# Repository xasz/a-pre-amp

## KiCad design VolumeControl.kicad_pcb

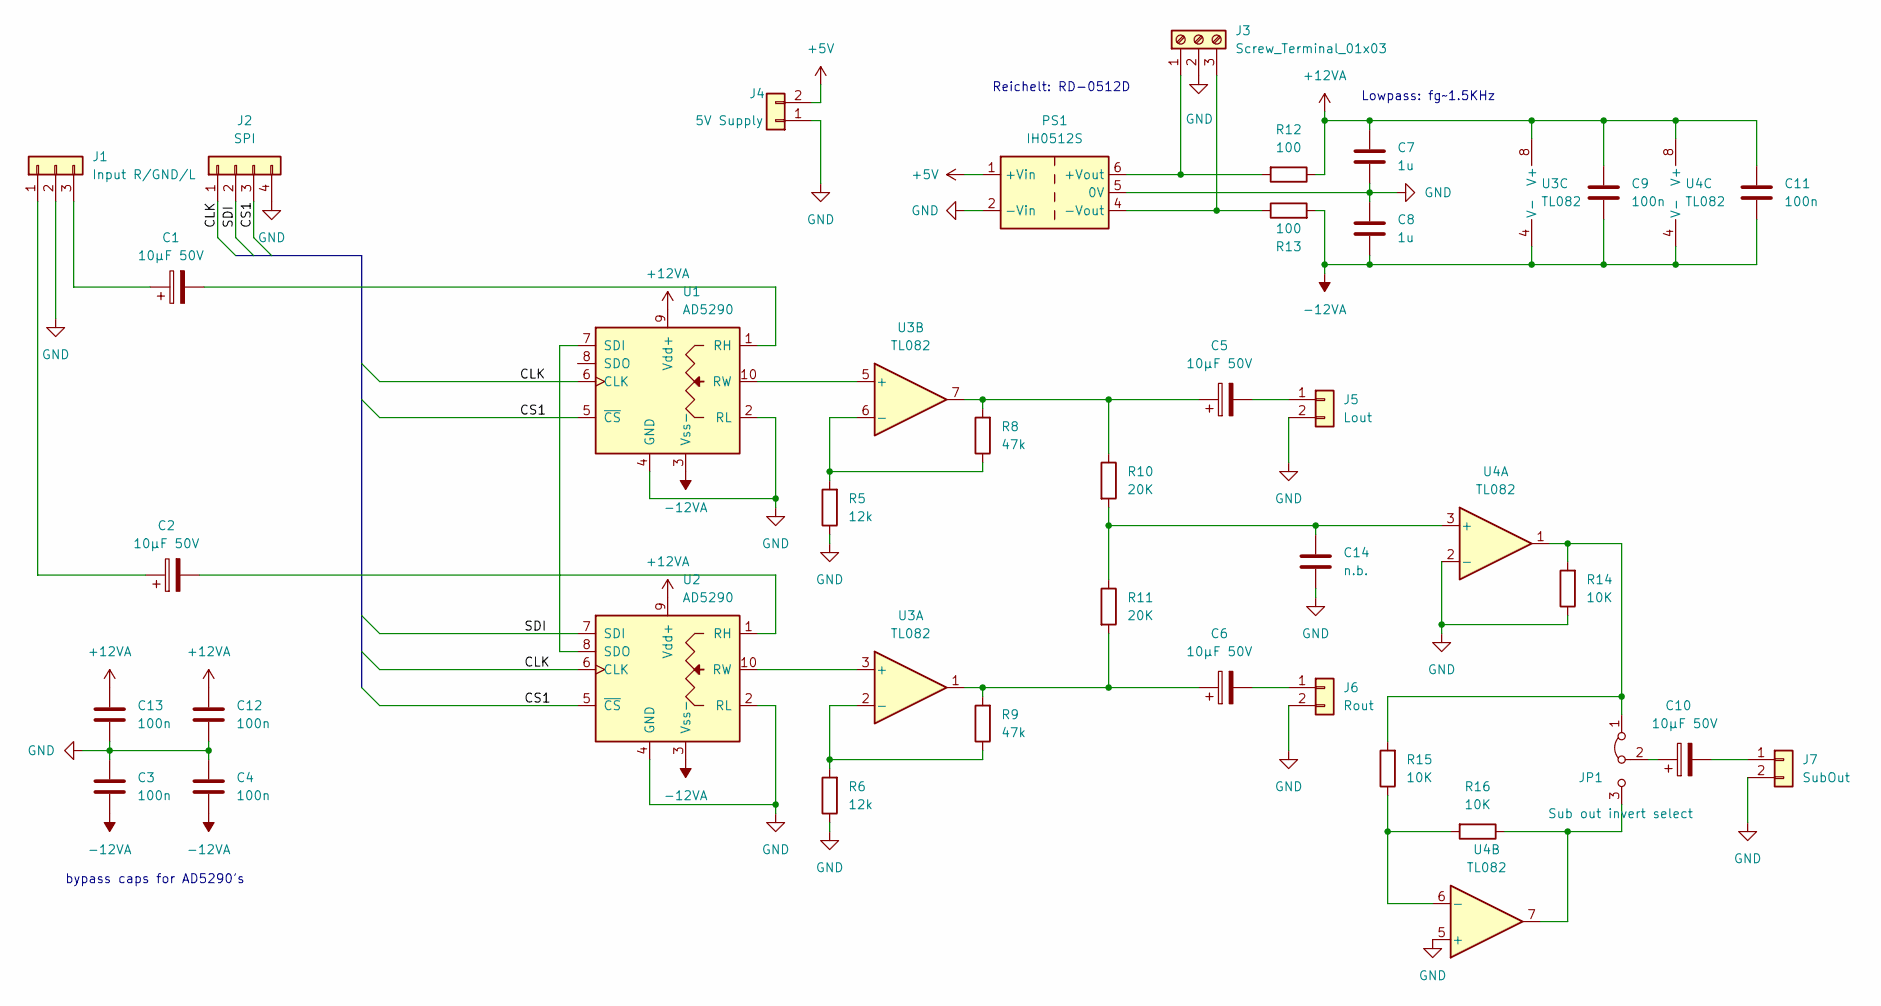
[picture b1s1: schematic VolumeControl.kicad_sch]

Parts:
C1, C2, C5, C6, C10: 10µF 50V; CP_Radial_D5.0mm_P2.00mm
C3, C4, C9, C11, C12, C13: 100n; C_Rect_L4.6mm_W2.0mm_P2.50mm_MKS02_FKP02
C7, C8: 1u; C_Rect_L7.0mm_W2.5mm_P5.00mm
C14: n.b.; C_Rect_L7.0mm_W2.5mm_P5.00mm
J1: Input R/GND/L; JST_XH_B3B-XH-A_1x03_P2.50mm_Vertical
J2: SPI; PinHeader_1x04_P2.54mm_Vertical
J3: Screw_Terminal_01x03; TerminalBlock_Phoenix_PT-1,5-3-5.0-H_1x03_P5.00mm_Horizontal
J4: 5V Supply; PinHeader_1x02_P2.54mm_Vertical
J5: Lout; Molex_KK-254_AE-6410-02A_1x02_P2.54mm_Vertical
J6: Rout; Molex_KK-254_AE-6410-02A_1x02_P2.54mm_Vertical
J7: SubOut; Molex_KK-254_AE-6410-02A_1x02_P2.54mm_Vertical
JP1: Sub out invert select; PinHeader_1x03_P2.54mm_Vertical
PS1: IH0512S; Converter_DCDC_XP_POWER-IHxxxxS_THT
R5, R6: 12k; R_Axial_DIN0207_L6.3mm_D2.5mm_P10.16mm_Horizontal
R8, R9: 47k; R_Axial_DIN0207_L6.3mm_D2.5mm_P10.16mm_Horizontal
R10, R11: 20K; R_Axial_DIN0207_L6.3mm_D2.5mm_P10.16mm_Horizontal
R12, R13: 100; R_Axial_DIN0207_L6.3mm_D2.5mm_P10.16mm_Horizontal
R14, R15, R16: 10K; R_Axial_DIN0207_L6.3mm_D2.5mm_P10.16mm_Horizontal
U1, U2: AD5290; MSOP-10_3x3mm_P0.5mm
U3, U4: TL082; DIP-8_W7.62mm_Socket

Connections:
+5V: J4.2, PS1.1 (+Vin)
+12VA: C7.1, C9.1, C11.1, C12.1, C13.1, R12.1, U1.9 (Vdd+), U2.9 (Vdd+), U3.8 (V+), U4.8 (V+)
-12VA: C3.2, C4.2, C8.2, C9.2, C11.2, R13.2, U1.3 (Vss-), U2.3 (Vss-), U3.4 (V-), U4.4 (V-)
/CLK: J2.1, U1.6 (CLK), U2.6 (CLK)
/CS1: J2.3, U1.5 (~CS), U2.5 (~CS)
/SDI: J2.2, U2.7 (SDI)
GND: C3.1, C4.1, C7.2, C8.1, C12.2, C13.2, C14.2, J1.2, J2.4, J3.2, J4.1, J5.2, J6.2, J7.2, PS1.2 (-Vin), PS1.5 (0V), R5.1, R6.1, R14.1, U1.2 (RL), U1.4 (GND), U2.2 (RL), U2.4 (GND), U4.2 (-), U4.5 (+)
unnamed: C1.1, J1.3
unnamed: C1.2, U1.1 (RH)
unnamed: C2.1, J1.1
unnamed: C2.2, U2.1 (RH)
unnamed: C5.1, R8.2, R10.1, U3.7
unnamed: C5.2, J5.1
unnamed: C6.1, R9.2, R11.2, U3.1
unnamed: C6.2, J6.1
unnamed: C10.1, JP1.2 (C)
unnamed: C10.2, J7.1
unnamed: C14.1, R10.2, R11.1, U4.3 (+)
unnamed: J3.1, PS1.6 (+Vout), R12.2
unnamed: J3.3, PS1.4 (-Vout), R13.1
unnamed: JP1.1 (A), R14.2, R15.2, U4.1
unnamed: JP1.3 (B), R16.1, U4.7
unnamed: R5.2, R8.1, U3.6 (-)
unnamed: R6.2, R9.1, U3.2 (-)
unnamed: R15.1, R16.2, U4.6 (-)
unnamed: U1.7 (SDI), U2.8 (SDO)
unnamed: U1.10 (RW), U3.5 (+)
unnamed: U2.10 (RW), U3.3 (+)

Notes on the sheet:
bypass caps for AD5290's
Reichelt: RD-0512D
Lowpass: fg~1.5KHz

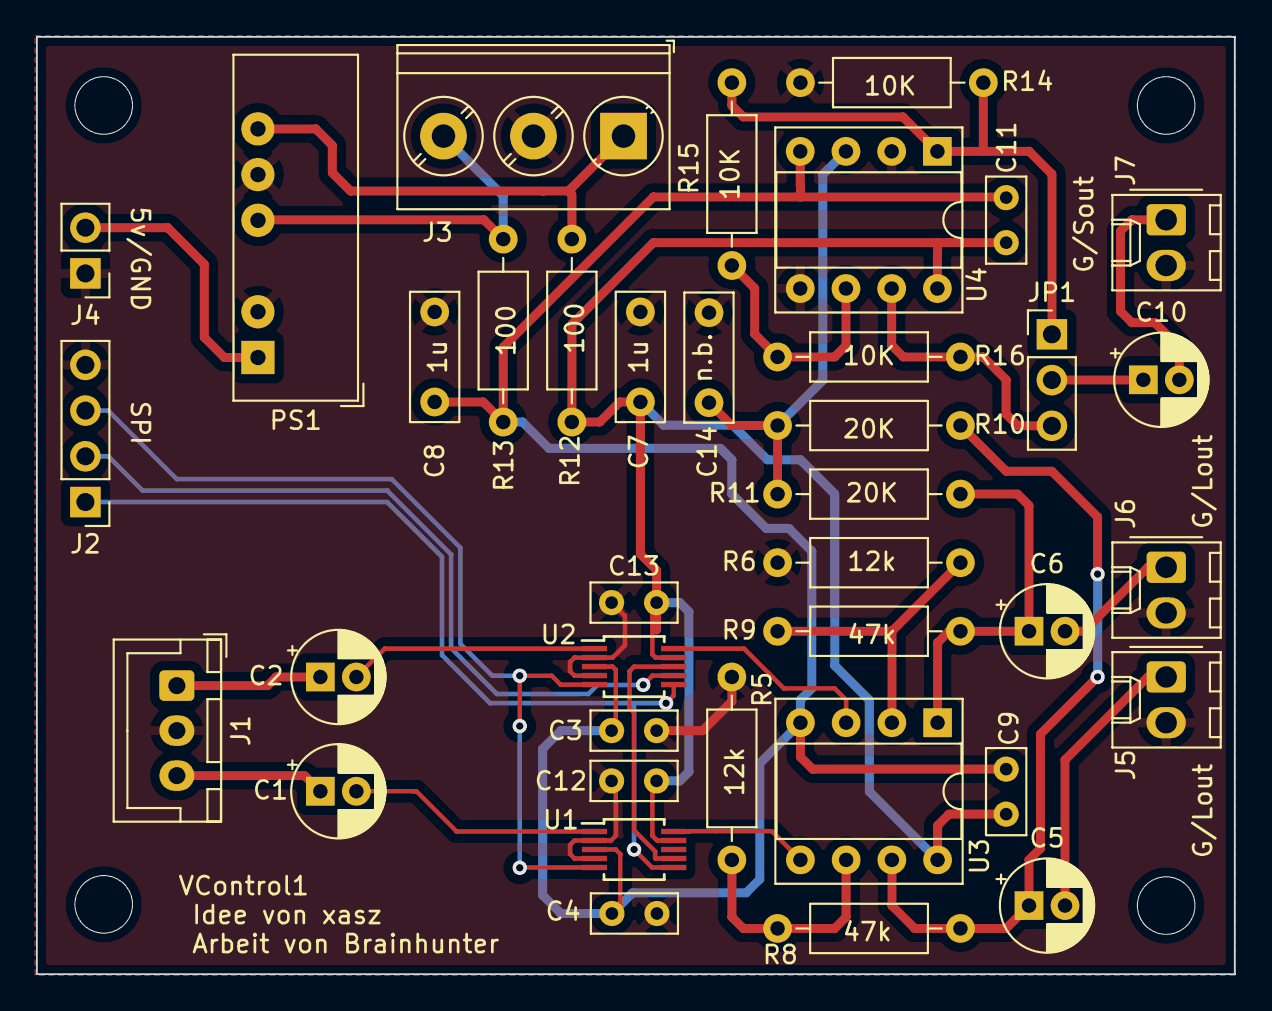
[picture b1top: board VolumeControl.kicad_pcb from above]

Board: 2 copper layers, 66.5 x 52.1 mm, 39 parts (0 on the bottom side), 28 nets.

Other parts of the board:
Ref**: MountingHole_3.2mm_M3

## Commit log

2022-01-23 I have no idea what i am doing
2022-01-23 some corrections
2022-01-27 Added Sub Out
2022-01-27 Added Power
2022-01-29 corrected schematic, selected footprints, created pcb file
2022-01-29 ähhhh
2022-01-30 corrected some issues in the schematic * added jumper for phase invert of the sub out * routed layout
2022-01-30 Revert "Create VolumeControl-2022-01-30_231548.zip"
    This reverts commit 8562aef6a532102224dfdae913b912fa46ba37f8.
2022-01-30 Added some Labels
2022-02-10 changed design to AD5290
2022-02-13 added bypass relais
2022-02-13 added backup folder to gitignore and removed files from the index
2022-02-13 Fixed DRC errors fine adjusted some positions Nice Silkscreen Gerber files exported
2022-02-21 First Order
